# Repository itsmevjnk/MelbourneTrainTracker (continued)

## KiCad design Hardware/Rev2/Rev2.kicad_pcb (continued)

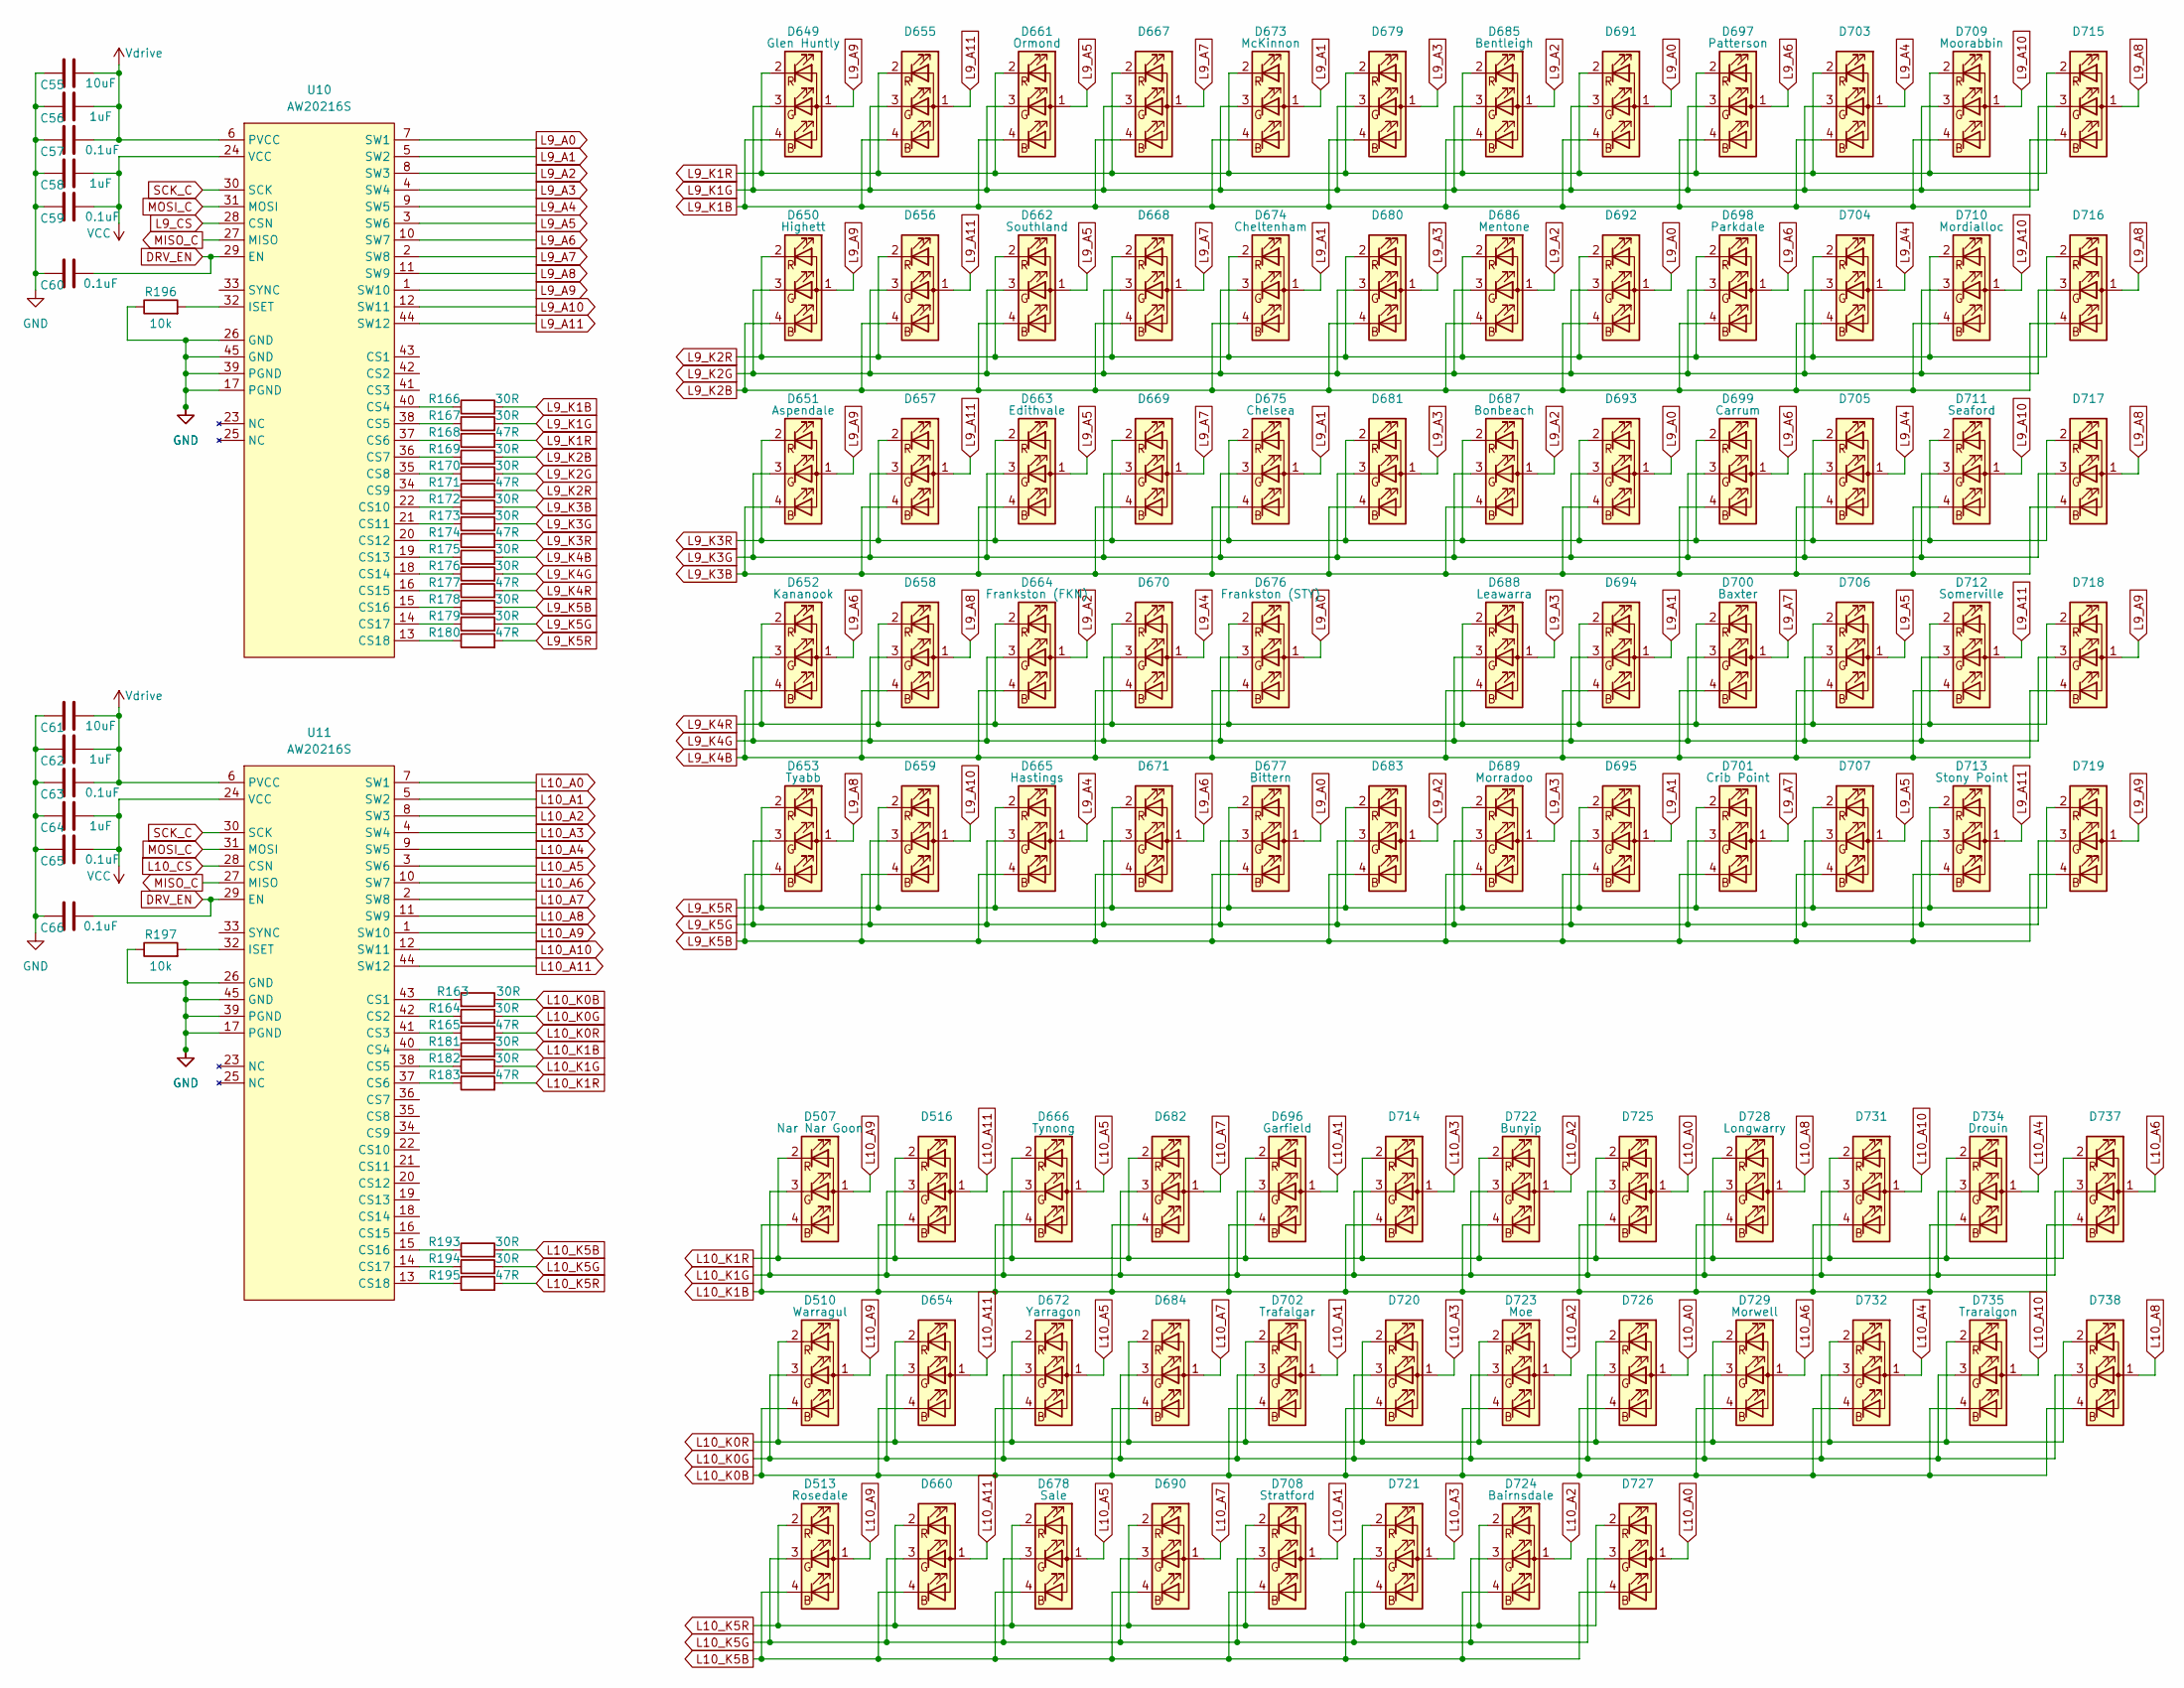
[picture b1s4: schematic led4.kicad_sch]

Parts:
C55, C61: 10uF; C_0805_2012Metric_Pad1.18x1.45mm_HandSolder; MPN C380332
C56, C58, C62, C64: 1uF; C_0603_1608Metric_Pad1.08x0.95mm_HandSolder; MPN C6119849
C57, C59, C60, C63, C65, C66: 0.1uF; C_0603_1608Metric_Pad1.08x0.95mm_HandSolder; MPN C14663
D507, D510, D513, D516, D649, D650, D651, D652, D653, D654, D655, D656, D657, D658, D659, D660, D661, D662, D663, D664, D665, D666, D667, D668, D669, D670, D671, D672, D673, D674, D675, D676, D677, D678, D679, D680, D681, D682, D683, D684, D685, D686, D687, D688, D689, D690, D691, D692, D693, D694, D695, D696, D697, D698, D699, D700, D701, D702, D703, D704, D705, D706, D707, D708, D709, D710, D711, D712, D713, D714, D715, D716, D717, D718, D719, D720, D721, D722, D723, D724, D725, D726, D727, D728, D729, D731, D732, D734, D735, D737, D738: XL-B1010RGBT-HF; LED_RGB_Xinglight-1010; MPN C22464515
R163, R164, R166, R167, R169, R170, R172, R173, R175, R176, R178, R179, R181, R182, R193, R194: 30R; R_0805_2012Metric_Pad1.20x1.40mm_HandSolder
R165, R168, R171, R174, R177, R180, R183, R195: 47R; R_0805_2012Metric_Pad1.20x1.40mm_HandSolder
R196, R197: 10k; R_0603_1608Metric_Pad0.98x0.95mm_HandSolder; MPN C15401
U10, U11: AW20216S; QFN-44-1EP_5x5mm_P0.4mm_EP2.45x2.45mm; MPN C7385556

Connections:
+3.3V: C58.2, C59.2, C64.2, C65.2, U10.24 (VCC), U11.24 (VCC); also elsewhere on the board
+5V: C55.2, C56.2, C57.2, C61.2, C62.2, C63.2, U10.6 (PVCC), U11.6 (PVCC); also elsewhere on the board
DRV_EN: C60.2, C66.2, U10.29 (EN), U11.29 (EN); also elsewhere on the board
GND: C55.1, C56.1, C57.1, C58.1, C59.1, C60.1, C61.1, C62.1, C63.1, C64.1, C65.1, C66.1, R196.1, R197.1, U10.17 (PGND), U10.26 (GND), U10.39 (PGND), U10.45 (GND), U11.17 (PGND), U11.26 (GND), U11.39 (PGND), U11.45 (GND); also elsewhere on the board
L9_A0: D676.1 (A), D677.1 (A), D691.1 (A), D692.1 (A), D693.1 (A), U10.7 (SW1)
L9_A1: D673.1 (A), D674.1 (A), D675.1 (A), D694.1 (A), D695.1 (A), U10.5 (SW2)
L9_A2: D664.1 (A), D683.1 (A), D685.1 (A), D686.1 (A), D687.1 (A), U10.8 (SW3)
L9_A3: D679.1 (A), D680.1 (A), D681.1 (A), D688.1 (A), D689.1 (A), U10.4 (SW4)
L9_A4: D665.1 (A), D670.1 (A), D703.1 (A), D704.1 (A), D705.1 (A), U10.9 (SW5)
L9_A5: D661.1 (A), D662.1 (A), D663.1 (A), D706.1 (A), D707.1 (A), U10.3 (SW6)
L9_A6: D652.1 (A), D671.1 (A), D697.1 (A), D698.1 (A), D699.1 (A), U10.10 (SW7)
L9_A7: D667.1 (A), D668.1 (A), D669.1 (A), D700.1 (A), D701.1 (A), U10.2 (SW8)
L9_A8: D653.1 (A), D658.1 (A), D715.1 (A), D716.1 (A), D717.1 (A), U10.11 (SW9)
L9_A9: D649.1 (A), D650.1 (A), D651.1 (A), D718.1 (A), D719.1 (A), U10.1 (SW10)
L9_A10: D659.1 (A), D709.1 (A), D710.1 (A), D711.1 (A), U10.12 (SW11)
L9_A11: D655.1 (A), D656.1 (A), D657.1 (A), D712.1 (A), D713.1 (A), U10.44 (SW12)
L9_CS: U10.28 (CSN); also elsewhere on the board
L9_K1B: D649.4 (BK), D655.4 (BK), D661.4 (BK), D667.4 (BK), D673.4 (BK), D679.4 (BK), D685.4 (BK), D691.4 (BK), D697.4 (BK), D703.4 (BK), D709.4 (BK), D715.4 (BK), R166.2
L9_K1G: D649.3 (GK), D655.3 (GK), D661.3 (GK), D667.3 (GK), D673.3 (GK), D679.3 (GK), D685.3 (GK), D691.3 (GK), D697.3 (GK), D703.3 (GK), D709.3 (GK), D715.3 (GK), R167.2
L9_K1R: D649.2 (RK), D655.2 (RK), D661.2 (RK), D667.2 (RK), D673.2 (RK), D679.2 (RK), D685.2 (RK), D691.2 (RK), D697.2 (RK), D703.2 (RK), D709.2 (RK), D715.2 (RK), R168.2
L9_K2B: D650.4 (BK), D656.4 (BK), D662.4 (BK), D668.4 (BK), D674.4 (BK), D680.4 (BK), D686.4 (BK), D692.4 (BK), D698.4 (BK), D704.4 (BK), D710.4 (BK), D716.4 (BK), R169.2
L9_K2G: D650.3 (GK), D656.3 (GK), D662.3 (GK), D668.3 (GK), D674.3 (GK), D680.3 (GK), D686.3 (GK), D692.3 (GK), D698.3 (GK), D704.3 (GK), D710.3 (GK), D716.3 (GK), R170.2
L9_K2R: D650.2 (RK), D656.2 (RK), D662.2 (RK), D668.2 (RK), D674.2 (RK), D680.2 (RK), D686.2 (RK), D692.2 (RK), D698.2 (RK), D704.2 (RK), D710.2 (RK), D716.2 (RK), R171.2
L9_K3B: D651.4 (BK), D657.4 (BK), D663.4 (BK), D669.4 (BK), D675.4 (BK), D681.4 (BK), D687.4 (BK), D693.4 (BK), D699.4 (BK), D705.4 (BK), D711.4 (BK), D717.4 (BK), R172.2
L9_K3G: D651.3 (GK), D657.3 (GK), D663.3 (GK), D669.3 (GK), D675.3 (GK), D681.3 (GK), D687.3 (GK), D693.3 (GK), D699.3 (GK), D705.3 (GK), D711.3 (GK), D717.3 (GK), R173.2
L9_K3R: D651.2 (RK), D657.2 (RK), D663.2 (RK), D669.2 (RK), D675.2 (RK), D681.2 (RK), D687.2 (RK), D693.2 (RK), D699.2 (RK), D705.2 (RK), D711.2 (RK), D717.2 (RK), R174.2
L9_K4B: D652.4 (BK), D658.4 (BK), D664.4 (BK), D670.4 (BK), D676.4 (BK), D688.4 (BK), D694.4 (BK), D700.4 (BK), D706.4 (BK), D712.4 (BK), D718.4 (BK), R175.2
L9_K4G: D652.3 (GK), D658.3 (GK), D664.3 (GK), D670.3 (GK), D676.3 (GK), D688.3 (GK), D694.3 (GK), D700.3 (GK), D706.3 (GK), D712.3 (GK), D718.3 (GK), R176.2
L9_K4R: D652.2 (RK), D658.2 (RK), D664.2 (RK), D670.2 (RK), D676.2 (RK), D688.2 (RK), D694.2 (RK), D700.2 (RK), D706.2 (RK), D712.2 (RK), D718.2 (RK), R177.2
L9_K5B: D653.4 (BK), D659.4 (BK), D665.4 (BK), D671.4 (BK), D677.4 (BK), D683.4 (BK), D689.4 (BK), D695.4 (BK), D701.4 (BK), D707.4 (BK), D713.4 (BK), D719.4 (BK), R178.2
L9_K5G: D653.3 (GK), D659.3 (GK), D665.3 (GK), D671.3 (GK), D677.3 (GK), D683.3 (GK), D689.3 (GK), D695.3 (GK), D701.3 (GK), D707.3 (GK), D713.3 (GK), D719.3 (GK), R179.2
L9_K5R: D653.2 (RK), D659.2 (RK), D665.2 (RK), D671.2 (RK), D677.2 (RK), D683.2 (RK), D689.2 (RK), D695.2 (RK), D701.2 (RK), D707.2 (RK), D713.2 (RK), D719.2 (RK), R180.2
L10_A0: D725.1 (A), D726.1 (A), D727.1 (A), U11.7 (SW1)
L10_A1: D696.1 (A), D702.1 (A), D708.1 (A), U11.5 (SW2)
L10_A2: D722.1 (A), D723.1 (A), D724.1 (A), U11.8 (SW3)
L10_A3: D714.1 (A), D720.1 (A), D721.1 (A), U11.4 (SW4)
L10_A4: D732.1 (A), D734.1 (A), U11.9 (SW5)
L10_A5: D666.1 (A), D672.1 (A), D678.1 (A), U11.3 (SW6)
L10_A6: D729.1 (A), D737.1 (A), U11.10 (SW7)
L10_A7: D682.1 (A), D684.1 (A), D690.1 (A), U11.2 (SW8)
L10_A8: D728.1 (A), D738.1 (A), U11.11 (SW9)
L10_A9: D507.1 (A), D510.1 (A), D513.1 (A), U11.1 (SW10)
L10_A10: D731.1 (A), D735.1 (A), U11.12 (SW11)
L10_A11: D516.1 (A), D654.1 (A), D660.1 (A), U11.44 (SW12)
L10_CS: U11.28 (CSN); also elsewhere on the board
L10_K0B: D510.4 (BK), D654.4 (BK), D672.4 (BK), D684.4 (BK), D702.4 (BK), D720.4 (BK), D723.4 (BK), D726.4 (BK), D729.4 (BK), D732.4 (BK), D735.4 (BK), D738.4 (BK), R163.1
L10_K0G: D510.3 (GK), D654.3 (GK), D672.3 (GK), D684.3 (GK), D702.3 (GK), D720.3 (GK), D723.3 (GK), D726.3 (GK), D729.3 (GK), D732.3 (GK), D735.3 (GK), D738.3 (GK), R164.2
L10_K0R: D510.2 (RK), D654.2 (RK), D672.2 (RK), D684.2 (RK), D702.2 (RK), D720.2 (RK), D723.2 (RK), D726.2 (RK), D729.2 (RK), D732.2 (RK), D735.2 (RK), D738.2 (RK), R165.2
L10_K1B: D507.4 (BK), D516.4 (BK), D666.4 (BK), D682.4 (BK), D696.4 (BK), D714.4 (BK), D722.4 (BK), D725.4 (BK), D728.4 (BK), D731.4 (BK), D734.4 (BK), D737.4 (BK), R181.2
L10_K1G: D507.3 (GK), D516.3 (GK), D666.3 (GK), D682.3 (GK), D696.3 (GK), D714.3 (GK), D722.3 (GK), D725.3 (GK), D728.3 (GK), D731.3 (GK), D734.3 (GK), D737.3 (GK), R182.2
L10_K1R: D507.2 (RK), D516.2 (RK), D666.2 (RK), D682.2 (RK), D696.2 (RK), D714.2 (RK), D722.2 (RK), D725.2 (RK), D728.2 (RK), D731.2 (RK), D734.2 (RK), D737.2 (RK), R183.2
L10_K5B: D513.4 (BK), D660.4 (BK), D678.4 (BK), D690.4 (BK), D708.4 (BK), D721.4 (BK), D724.4 (BK), D727.4 (BK), R193.2
L10_K5G: D513.3 (GK), D660.3 (GK), D678.3 (GK), D690.3 (GK), D708.3 (GK), D721.3 (GK), D724.3 (GK), D727.3 (GK), R194.2
L10_K5R: D513.2 (RK), D660.2 (RK), D678.2 (RK), D690.2 (RK), D708.2 (RK), D721.2 (RK), D724.2 (RK), D727.2 (RK), R195.2
MISO_C: U10.27 (MISO), U11.27 (MISO); also elsewhere on the board
MOSI_C: U10.31 (MOSI), U11.31 (MOSI); also elsewhere on the board
unnamed: R166.1, U10.40 (CS4)
unnamed: R167.1, U10.38 (CS5)
unnamed: R168.1, U10.37 (CS6)
unnamed: R169.1, U10.36 (CS7)
unnamed: R170.1, U10.35 (CS8)
unnamed: R171.1, U10.34 (CS9)
unnamed: R172.1, U10.22 (CS10)
unnamed: R173.1, U10.21 (CS11)
unnamed: R174.1, U10.20 (CS12)
unnamed: R175.1, U10.19 (CS13)
unnamed: R176.1, U10.18 (CS14)
unnamed: R177.1, U10.16 (CS15)
unnamed: R178.1, U10.15 (CS16)
unnamed: R179.1, U10.14 (CS17)
unnamed: R180.1, U10.13 (CS18)
unnamed: R196.2, U10.32 (ISET)
unnamed: R163.2, U11.43 (CS1)
unnamed: R164.1, U11.42 (CS2)
unnamed: R165.1, U11.41 (CS3)
unnamed: R181.1, U11.40 (CS4)
unnamed: R182.1, U11.38 (CS5)
unnamed: R183.1, U11.37 (CS6)
unnamed: R193.1, U11.15 (CS16)
unnamed: R194.1, U11.14 (CS17)
unnamed: R195.1, U11.13 (CS18)
unnamed: R197.2, U11.32 (ISET)
SCK_C: U10.30 (SCK), U11.30 (SCK); also elsewhere on the board

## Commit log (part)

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2025-05-03 initial commit with LED flash
2025-05-03 add AW20216S init code
2025-05-03 add LED pins and cycle through colours
2025-05-03 remove Sandringham from Frankston line, which is added by mistake
2025-05-03 make colours look better
    might be a bit dim
2025-05-03 add custom partition table
2025-05-03 implement persistent configuration using NVS and configuration CLI
2025-05-03 implement time synchronisation
2025-05-03 update GTFS dataset to postgres db
2025-05-03 add daily timetable initialisation, to be run at 3AM everyday
2025-05-03 add next station to daily timetable
2025-05-03 implement MQTT message publishing
    note that our deployment should use a dedicated MQTT broker with proper perms
2025-05-04 simplify event filtering
2025-05-04 publish adjacent station on both sides (prev and next)
2025-05-04 show MQTT message length for ease of tuning
2025-05-04 handle service cancellations
2025-05-04 add adjacent station arrival/departure timestamp to handle multiple LEDs between stations
2025-05-06 prototype, still having problems
    - random trains get "teleported" to Craigieburn???
    - memory leaks hard
2025-05-06 clamp LED index
2025-05-06 reverse Laverton express LED order
2025-05-06 clear m_updatesMap after committing updates, seems to resolve memory leak
2025-05-06 set flash size to 4M
2025-05-07 add option for running all LED drivers from SPI3/VSPI
2025-05-07 switch to vanilla ESP-IDF from PlatformIO
2025-05-07 rename TAG to kTag for consistency
2025-05-07 handle no row updates from GTFS Realtime (which happens as there are no services left during the night)
2025-05-08 better(?) state update algorithm, not stable though
2025-05-08 fix incorrect assertion
2025-05-08 acquire states for the entirety of the update process
2025-05-08 show MQTT broker in configuration CLI
2025-05-08 make message publishing its own thing so we can send mock data
2025-05-08 get adjacent stations and timestamps on the fly to easily ensure consistency as the timetable is updated
2025-05-08 make transition between intermediary LEDs smoother
2025-05-08 rollback conditional updating and hopefully fix disappearing trains... hopefully
2025-05-08 add test script to send mock data
2025-05-08 fix reallocation assertion for when there are no entries on boot
2025-05-08 attempt to bring back conditional updating
2025-05-09 fix critical unbounded read on FSS-RMD
2025-05-09 implement strict colour checking to catch corruptions
2025-05-09 correctly handle discontinuous seq in GTFS timetable
2025-05-09 clean up main.cpp
2025-05-09 add Kconfig for easier firmware config
2025-05-09 make state update configurable
2025-05-09 batch insertions to make backend runnable on Oracle Cloud
2025-05-09 set default MQTT broker to the production server
2025-05-09 use error LED to indicate MQTT errors
2025-05-10 add departure discovery
2025-05-11 use departure discovery info to find run refs for GTFS trip IDs that do not exist in static data
2025-05-11 update database init script
2025-05-11 specify timezone in SQL init script
2025-05-11 fix daily fetch time
2025-05-11 preseed with more termini to maximise coverage
2025-05-11 add CAM, NME and CFD to preseed
2025-05-12 allow PTV Timetable API to be effectively used to substitute GTFS updates
    still need to handle mismatching departure sequence numbers (due to express services)
2025-05-13 add API endpoints for turning LED drivers on/off
2025-05-13 implement mDNS
2025-05-13 broadcast LED matrix buffer over WebSocket
2025-05-13 properly initialise fds since this is read by httpd_get_client_list
2025-05-14 start adding board view
2025-05-18 add LED offset map to board script
2025-05-18 finalise board view functionality
2025-05-18 update GTFS dataset URL
    why did this change though :/
2025-05-18 fix LED offsets
2025-05-19 add complete motion sensing code
2025-05-19 make activation duration configurable
2025-05-19 add blinking LED in config mode
2025-05-20 control LED driver phase to smooth out load
    will probably need more testing
2025-05-20 add web admin interface
2025-05-23 add hardware schematic and PCB layout
2025-05-24 update PIR sensor pin
2025-05-29 update for new GTFS-R feed
2025-05-29 add build script
2025-08-06 fix SPI bus definitions
2025-10-15 update GTFS feed URLs
2025-10-15 fix config defines
    apparently all sdkconfig items have CONFIG_ automatically prepended
2025-10-16 add GTFS-R decoding, kind of works but running out of heap too quickly
2025-10-16 read response directly to protobuf decoder instead of saving to intermediate buffer
2025-10-16 add response fragment buffer to speed up fetches
2025-10-16 move non-template functions from header to source
2025-10-16 make stop ID buffer length 20 bytes
    in case we ever get insanities like vic:rail:ALM_ConX
2025-10-16 create GTFS-R update task
2025-10-16 decode trip and stop IDs, and hash trip ID for reference
    also added stop ID lookup table generator script
2025-10-17 implement dry run to count elements for preallocation
2025-10-17 V/Line finally working
2025-10-17 change Caroline Springs code from CPS to RVH
2025-10-17 clean up tables and use 4 letters for station codes to handle -V suffixes
    this also requires increasing the infrastructure ID length to 4 bytes
2025-10-17 update GTFS dataset URL
2025-10-17 suppress unknown alert logs
2025-10-17 remove PTV Timetable API support
    now that GTFS-R is actually good, we don't need it anymore
2025-10-20 remove deprecated vPK code for V/Line Pakenham line
    this no longer exists in the GTFS feeds
2025-10-20 add V/Line GTFS-R endpoints
2025-10-20 obtain GTFS dataset URL by scraping
2025-10-21 add backend Docker build+push workflow
    this commit was created in the Dandenong Ranges btw :)
2025-10-21 add firmware build workflow
2025-11-30 fix race condition when parsing GTFS dataset
    not sure why the code worked previously :/ also happy Munnel opening!
2025-11-30 add Metro Tunnel station codes
2025-12-01 add Metro Tunnel handling
2025-12-02 add new Rev2 board using ESP32-S3
    no SD card slot though, not that we may need it anyway (hopefully)
2025-12-03 add more vias and also KiCad logo
2025-12-03 add power LED
2025-12-03 add OSHW logo on PCB back
2025-12-07 change default Metro Tunnel service colour handling to use blue for all Metro Tunnel services
2025-12-08 Malvern station hack for Rev1 board
2025-12-08 add 3D models, and change USB-C connector type
2025-12-09 add header for SD card pins
2025-12-09 hopefully final board design
2025-12-12 allow pressing BOOT button to access configuration interface
2025-12-12 start Wi-Fi AP for configuration
2025-12-12 add API endpoints for reading MAC addresses
2025-12-13 make Wi-Fi certificate handling more robust
2025-12-13 add Wi-FI configuration API endpoints, as well as remote reset
2025-12-14 precompress static files with gzip for even smaller binary size
2025-12-14 fix line enable/disable, and also support the Metro Tunnel
2025-12-14 add uptime and build time API endpoints, and show additional info in web interface
2025-12-25 first batch
2025-12-28 add config webpage
2025-12-28 make info retrieval sequential to not stress the ESP32 out
2025-12-28 ignore clangd cache
2026-01-06 config stuff for newly arrived rev2 board, no LED offsets yet
2026-01-06 move LED matrix offsets to revision-specific directories
2026-01-06 silkscreen fixes
2026-01-07 Burnley group LED offsets
2026-01-07 Dandenong group LED offsets, and also fix rev1 hacks
2026-01-07 Metro Tunnel LED offsets
2026-01-07 Sandringham line LED offsets
2026-01-07 fix Armadale, Toorak and Hawksburn (Frankston line) LED wiring, and add Northern group LED offsets
    will need to run bodge wires for 1st batch boards
2026-01-07 V/Line LED offsets for Ballarat, Geelong and Gippsland lines, as well as handling code for regional services on these lines
    will need to add the remaining lines too
2026-01-08 add option to run bodge test prior to booting
    this will be used during production only
2026-01-09 call mbyGetLED instead of artGetLED for Maryborough line
2026-01-10 Bendigo and Seymour LED offsets and handling
2026-01-10 revision 2B board: fixed SD card wiring
2026-01-11 add rev2 board view, and also add gzip compression to build pipeline
2026-01-11 rebrand to Victorian Train Tracker
2026-01-11 flip colour order for rev2 board
2026-01-11 add OTA partition tables for ESP32 and ESP32S3
2026-01-21 make gzip_compress.py executable
    hopefully GitHub Actions would be happy with this
2026-01-21 add ESP32S3 GitHub Actions workflow
2026-01-21 remove rogue rev2 header includes
    must have been Cursor auto include thing acting up
2026-01-21 fix workflow mixup
2026-01-21 restore config.htm, and also change build timestamp to build revision
    not really related to OTA, but we'll be using this as a more reliable versioning strategy anyway
2026-01-21 add weekly update check job
2026-01-21 fix GitHub Actions workflow names, and also upload more binaries
2026-01-21 add status code check for update checking routine
2026-01-21 increase main task stack size to prevent glitches (hopefully)
2026-01-21 reset all LED drivers before enabling drivers
2026-02-10 change Bendigo line to use Echuca line instead, since some trains actually terminate in Epsom
2026-02-11 rename cross city LED colour to Frankston
2026-02-11 join Newport line up with Sandringham
2026-02-11 change Maryborough station code from MBY to MYB
2026-02-11 rename Eaglehawk and Garfield station codes to EHK and GFD
2026-02-11 change Springhurst station code to SHT
2026-02-13 change default NTP server to time.google.com
    seems to be more stable than pool.ntp.org
2026-02-15 fetch sequence number from stopping patterns
2026-02-15 fix arrival/departure time constraint
2026-02-15 prefix rail replacement bus trips with RRB
2026-02-15 publish rail replacement bus flag on MQTT
2026-02-15 fix crashes on subsequent updates
2026-02-17 discard update entries whose station cannot be resolved
2026-02-17 change disruption/RRB colour to be more orange
2026-02-17 implement reverse correction for correct displaying on web interface
2026-02-18 move forward and reverse LUTs to constexpr so they get computed at compile time
2026-02-18 make stop pattern part of daily cache too
    in case MTM is truly incompetent
2026-02-19 move RRB check to SQL query
2026-02-20 add workaround for Sunbury short workings not going through city
2026-02-23 resample to 25fps for better timing, and use indicator LEDs for sync
2026-03-16 extract station names from GTFS for mapping to station codes
2026-03-16 pull Stony Point timetable from MTM
2026-03-16 deduplicate RRB updates, should work now
2026-03-16 run OTA update in separate task with sufficient stack space (tested)
2026-04-04 refactor HTTP client element from OTA
2026-04-05 implement brightness control (untested)
2026-04-06 add API endpoints for setting brightness config
2026-04-12 fix crashes occurring when m_nextTime == m_time (hopefully)
2026-04-19 make line bitmask 64-bit
    fixes bug #36
2026-05-26 switch to hatched fill
2026-05-27 add +5V rail to debug header
    someone might want to power the board that way :/
2026-06-16 rev.2c revised PCB layout, final
2026-06-17 WIP - doesn't work right now, but we'll get back to it
2026-06-17 minor cleanups
2026-06-17 oops
2026-06-20 add wifi network scanning
2026-06-23 add config mode and init display
    also added QR code display, very cool
2026-06-24 run OLED I2C interface in fast mode for faster updating
